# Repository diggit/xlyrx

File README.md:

# xlyrx
Hobby RC 2.4GHz receiver based on cc2500 and STM32, supporting FrSky 2 Way D-series protocol

This project is another opensource receiver for cc2500 based radios.

## Features
- FrSky 2-way (telemetry) protocol for D-series
- based on ARM MCU (STM32)
- Hardware generated high resolution ppm signal (~4 times higher, than FrSky can tranfer)
- bind time RX-TX frequency offset elimination
- high power power amplifier and high sensitivity low noise amplifier cc2500 module
- alternative power input for channels 5,6,7,8
- 2 analog inputs
- initial work on fail-safes, when signal is lost, outputs are tuned off now, user config is missing

*ready, but hardcoded for now*
- configurable ppm frequency
	- channels 1,2,5,6 are driven by one HW timer, outputs 4,5,7,8 are driven by another
	- ppm frequency is defined by 3rd timer, all channels have same frequency for now, to be able to have different ppm frequency for each group, packet timeout timer must be changed from regular timer to systick, then we'll have free HW timer to drive second group of outputs with different frequency

*HW ready, SW not yet written*
- UART (3,3V) for loading new firmware (bootloader) and RX user configuration
- UART (3,3V) for external telemetry configuration (raw or FrSky format)
- meaningful usage of LED (we have 2 of them, so use them!)

### Known issues
- if TX and RX are too close during binding, binding may not be successful (stuck in binding mode)
	- maybe some AGC tuning could help
	- workaround would be binding procedure restart

## Why?
If you sum up all that time, materials and work, why (I) build this and not buy regular FrSky receiver? For fun! To explore HW, skills... I like the possibility to modify things to way I like them. Easily add new features and make them better than regular ones...

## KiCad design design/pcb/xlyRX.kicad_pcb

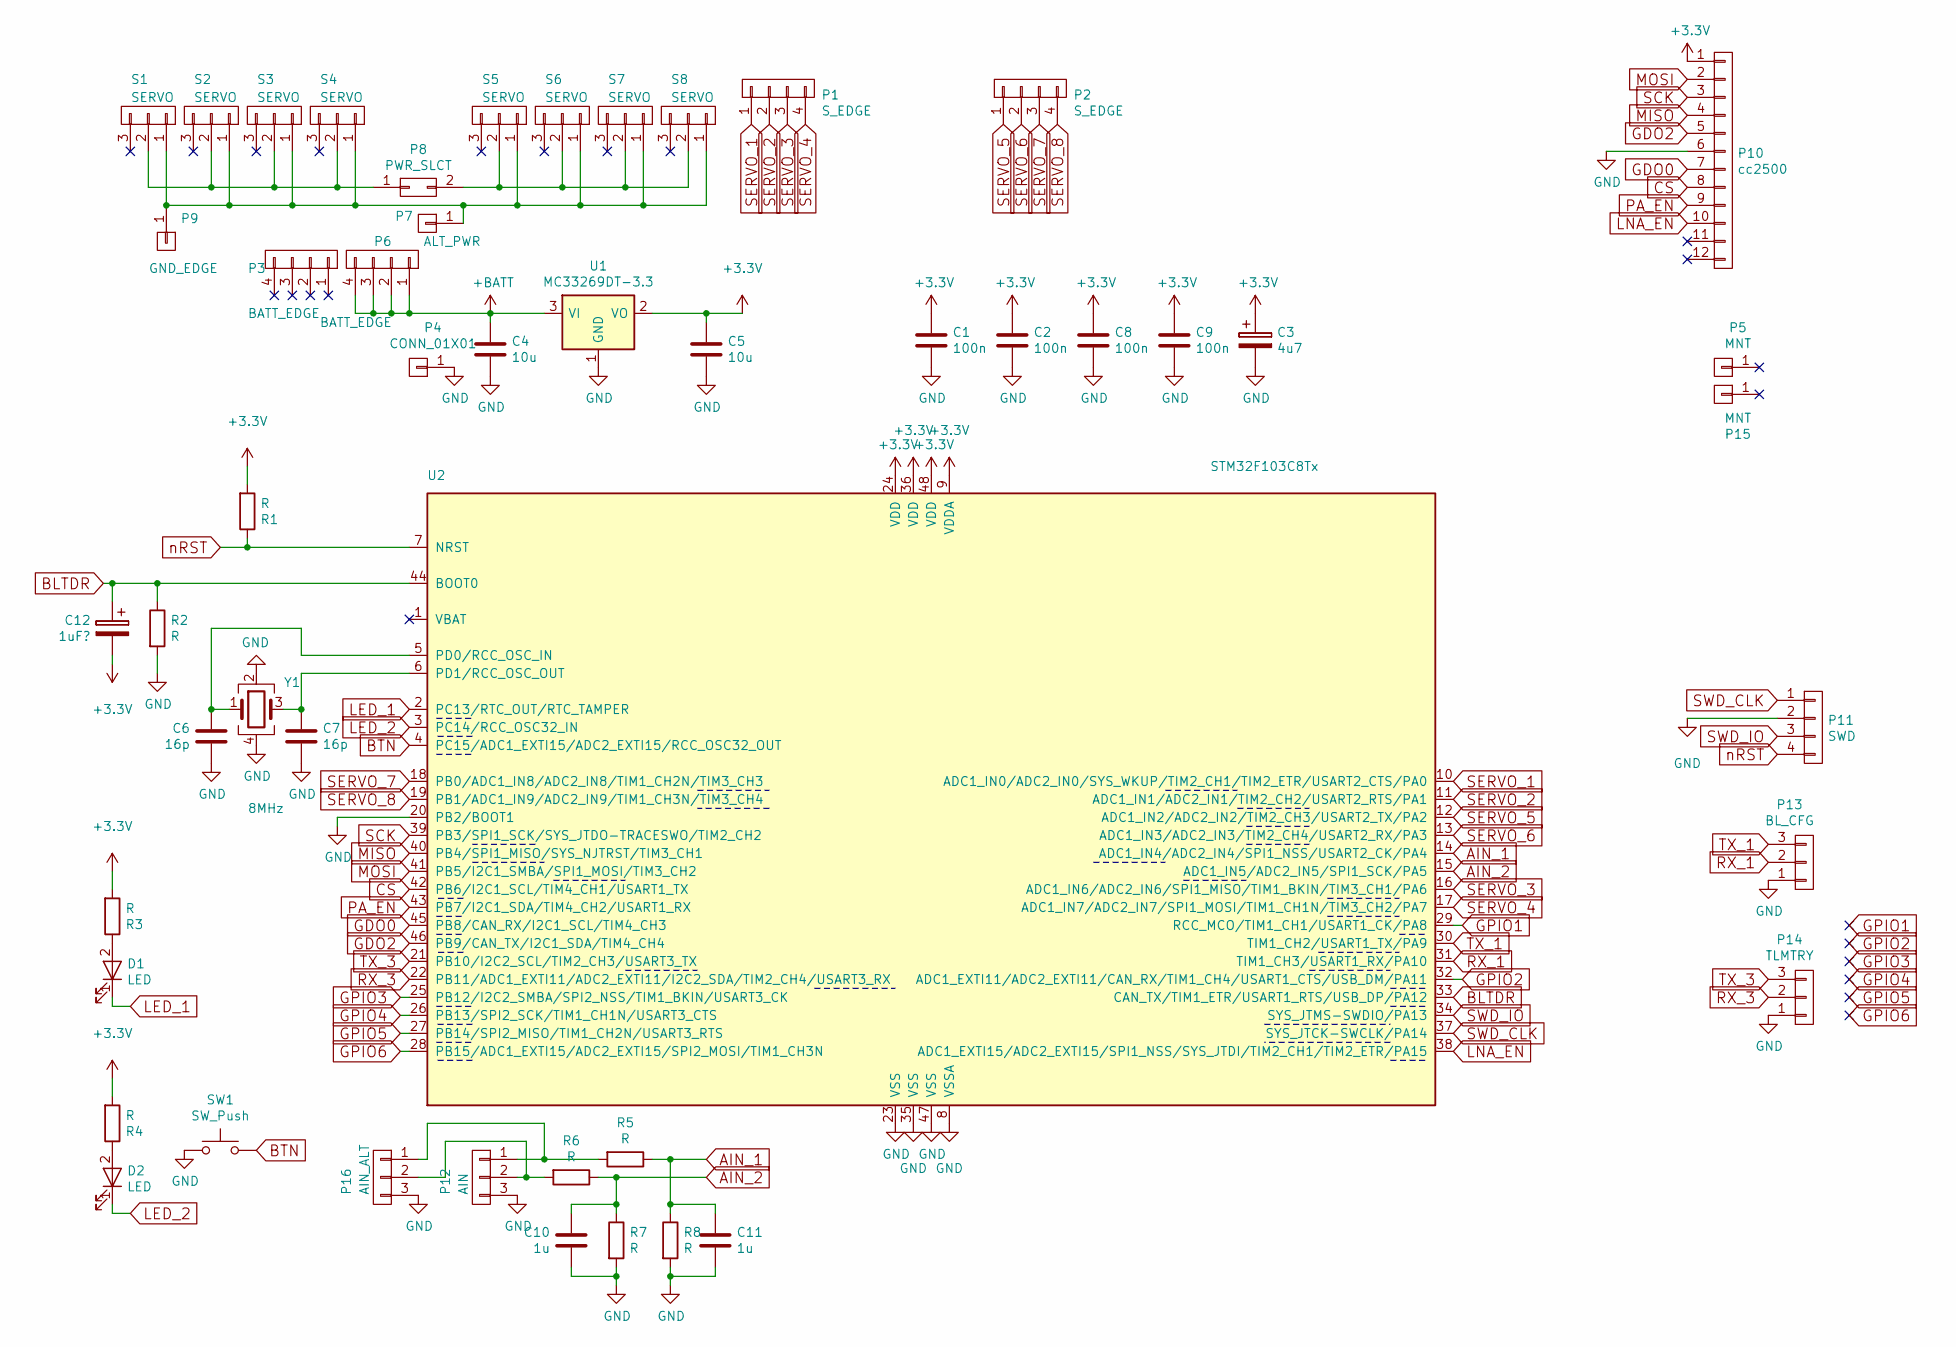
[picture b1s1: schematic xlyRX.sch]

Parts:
C1, C2, C8, C9: 100n; C_0805
C3: 4u7; C_0805
C4, C5: 10u; C_0805
C6, C7: 16p; C_0805
C10, C11: 1u; C_0805
C12: 1uF?; C_0805
D1, D2: LED; LED_0805
P1, P2: S_EDGE; SMD_conn_edge
P3, P6: BATT_EDGE; SMD_conn_edge
P4: CONN_01X01; SMD_conn_edge_1p
P5, P15: MNT; SMD_conn_edge_1p
P7: ALT_PWR; Pin_Header_Straight_1x01_Pitch2.54mm_simplified_silk
P8: PWR_SLCT; Pin_Header_Straight_1x02_Pitch2.54mm_simplified_silk
P9: GND_EDGE; SMD_conn_edge_1p
P10: cc2500; module_cc2500_PA_LNA_small_pads
P11: SWD; SMD_conn_edge
P12: AIN; SMD_conn_edge_3
P13: BL_CFG; Pin_Header_Straight_1x03
P14: TLMTRY; Pin_Header_Straight_1x03
P16: AIN_ALT; Pin_Header_Straight_1x03_Pitch2.54mm
R1, R2, R3, R4, R5, R6, R7, R8: R; R_0805
S1, S2, S3, S4, S5, S6, S7, S8: SERVO; Pin_Header_Straight_1x03_Pitch2.54mm_simplified_silk
SW1: SW_Push; SW_SPST_REED_CT05-XXXX-J1
U1: MC33269DT-3.3; TO-252-2Lead
U2: STM32F103C8Tx; LQFP-48_7x7mm_Pitch0.5mm
Y1: 8MHz; Crystal_SMD_5032_4Pads

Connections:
+3V3: C1.1, C2.1, C3.1, C5.1, C8.1, C9.1, C12.2, P10.1, R1.2, R3.2, R4.2, U1.2 (VO), U2.9 (VDDA), U2.24 (VDD), U2.36 (VDD), U2.48 (VDD)
+BATT: C4.1, P6.1, P6.2, P6.3, P6.4, U1.3 (VI)
AIN_1: C11.1, R5.1, R8.1, U2.14 (ADC1_IN4/ADC2_IN4/SPI1_NSS/USART2_CK/PA4)
AIN_2: C10.1, R6.1, R7.1, U2.15 (ADC1_IN5/ADC2_IN5/SPI1_SCK/PA5)
BLTDR: C12.1, R2.1, U2.33 (CAN_TX/TIM1_ETR/USART1_RTS/USB_DP/PA12), U2.44 (BOOT0)
BTN: SW1.2, U2.4 (PC15/ADC1_EXTI15/ADC2_EXTI15/RCC_OSC32_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)
CS: P10.8, U2.42 (PB6/I2C1_SCL/TIM4_CH1/USART1_TX)
GDO0: P10.7, U2.45 (PB8/CAN_RX/I2C1_SCL/TIM4_CH3)
GDO2: P10.5, U2.46 (PB9/CAN_TX/I2C1_SDA/TIM4_CH4)
GND: C1.2, C2.2, C3.2, C4.2, C5.2, C6.2, C7.2, C8.2, C9.2, C10.2, C11.2, P4.1, P10.6, P11.2, P12.3, P13.1, P14.1, P16.3, R2.2, R7.2, R8.2, SW1.1, U1.1 (GND), U2.8 (VSSA), U2.20 (PB2/BOOT1), U2.23 (VSS), U2.35 (VSS), U2.47 (VSS), Y1.2, Y1.4
GPIO1: U2.29 (RCC_MCO/TIM1_CH1/USART1_CK/PA8)
GPIO2: U2.32 (ADC1_EXTI11/ADC2_EXTI11/CAN_RX/TIM1_CH4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)
GPIO3: U2.25 (PB12/I2C2_SMBA/SPI2_NSS/TIM1_BKIN/USART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)
GPIO4: U2.26 (PB13/SPI2_SCK/TIM1_CH1N/USART3_CTS)
GPIO5: U2.27 (PB14/SPI2_MISO/TIM1_CH2N/USART3_RTS)
GPIO6: U2.28 (PB15/ADC1_EXTI15/ADC2_EXTI15/SPI2_MOSI/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)
LED_1: D1.1 (K), U2.2 (PC13/RTC_OUT/RTC_TAMPER)
LED_2: D2.1 (K), U2.3 (PC14/RCC_OSC32_IN)
LNA_EN: P10.10, U2.38 (ADC1_EXTI15/ADC2_EXTI15/SPI1_NSS/SYS_JT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)
MISO: P10.4, U2.40 (PB4/SPI1_MISO/SYS_NJTRST/TIM3_CH1)
MOSI: P10.2, U2.41 (PB5/I2C1_SMBA/SPI1_MOSI/TIM3_CH2)
unnamed: C6.1, U2.5 (PD0/RCC_OSC_IN), Y1.1
unnamed: C7.1, U2.6 (PD1/RCC_OSC_OUT), Y1.3
unnamed: D1.2 (A), R3.1
unnamed: D2.2 (A), R4.1
unnamed: P7.1, P9.1, S1.1, S2.1, S3.1, S4.1, S5.1, S6.1, S7.1, S8.1
unnamed: P8.1, S1.2, S2.2, S3.2, S4.2
unnamed: P8.2, S5.2, S6.2, S7.2, S8.2
unnamed: P12.1, P16.1, R5.2
unnamed: P12.2, P16.2, R6.2
PA_EN: P10.9, U2.43 (PB7/I2C1_SDA/TIM4_CH2/USART1_RX)
RX_1: P13.2, U2.31 (TIM1_CH3/USART1_RX/PA10)
RX_3: P14.2, U2.22 (PB11/ADC1_EXTI11/ADC2_EXTI11/I2C2_SDA/T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)
SCK: P10.3, U2.39 (PB3/SPI1_SCK/SYS_JTDO-TRACESWO/TIM2_CH2)
SERVO_1: P1.1, U2.10 (ADC1_IN0/ADC2_IN0/SYS_WKUP/TIM2_CH1/TIM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)
SERVO_2: P1.2, U2.11 (ADC1_IN1/ADC2_IN1/TIM2_CH2/USART2_RTS/P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)
SERVO_3: P1.3, U2.16 (ADC1_IN6/ADC2_IN6/SPI1_MISO/TIM1_BKIN/T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)
SERVO_4: P1.4, U2.17 (ADC1_IN7/ADC2_IN7/SPI1_MOSI/TIM1_CH1N/T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)
SERVO_5: P2.1, U2.12 (ADC1_IN2/ADC2_IN2/TIM2_CH3/USART2_TX/PA2)
SERVO_6: P2.2, U2.13 (ADC1_IN3/ADC2_IN3/TIM2_CH4/USART2_RX/PA3)
SERVO_7: P2.3, U2.18 (PB0/ADC1_IN8/ADC2_IN8/TIM1_CH2N/TIM3_CH3)
SERVO_8: P2.4, U2.19 (PB1/ADC1_IN9/ADC2_IN9/TIM1_CH3N/TIM3_CH4)
SWD_CLK: P11.1, U2.37 (SYS_JTCK-SWCLK/PA14)
SWD_IO: P11.3, U2.34 (SYS_JTMS-SWDIO/PA13)
TX_1: P13.3, U2.30 (TIM1_CH2/USART1_TX/PA9)
TX_3: P14.3, U2.21 (PB10/I2C2_SCL/TIM2_CH3/USART3_TX)
nRST: P11.4, R1.1, U2.7 (NRST)

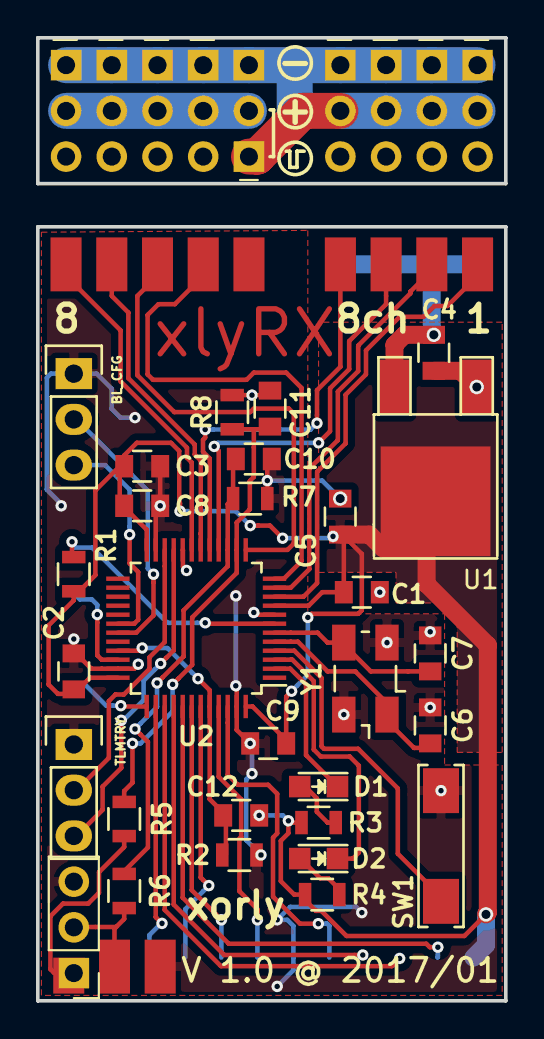
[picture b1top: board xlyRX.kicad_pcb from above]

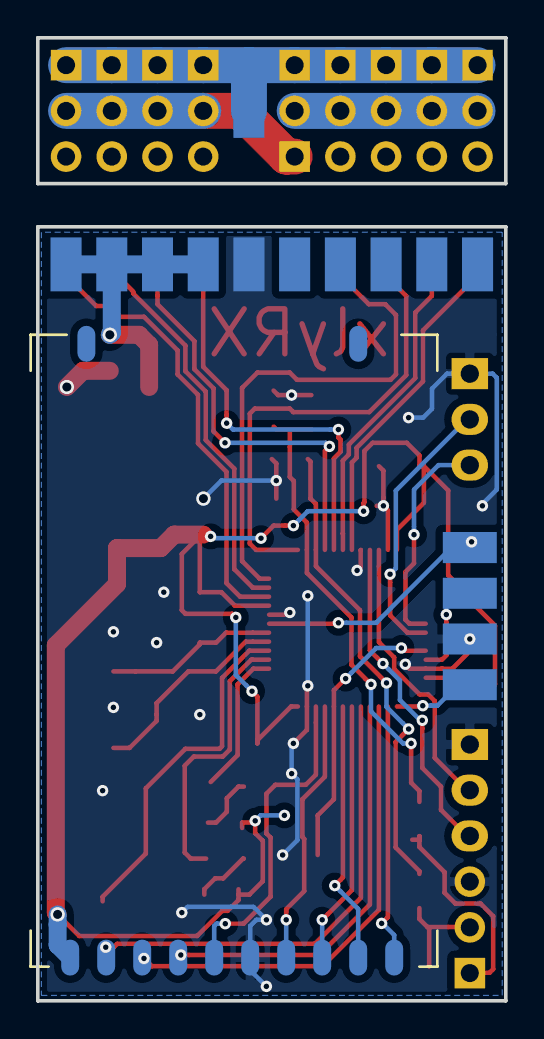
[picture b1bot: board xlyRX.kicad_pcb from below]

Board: 2 copper layers, 26.0 x 53.5 mm, 50 parts (7 on the bottom side), 41 nets.

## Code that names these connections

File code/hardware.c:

// Copyright (c) 2017 Patrik Bachan
//
// GNU GENERAL PUBLIC LICENSE
//    Version 3, 29 June 2007
//
// This program is free software: you can redistribute it and/or modify
// it under the terms of the GNU General Public License as published by
// the Free Software Foundation, either version 3 of the License, or
// (at your option) any later version.
//
// This program is distributed in the hope that it will be useful,
// but WITHOUT ANY WARRANTY; without even the implied warranty of
// MERCHANTABILITY or FITNESS FOR A PARTICULAR PURPOSE.  See the
// GNU General Public License for more details.
//
// You should have received a copy of the GNU General Public License
// along with this program.  If not, see <http://www.gnu.org/licenses/>.

#include "hardware.h"
#include "misc.h"


void gpio_init(void)
{
	bit_set(RCC->APB2ENR, \
			RCC_APB2ENR_IOPAEN |\
			RCC_APB2ENR_IOPBEN |\
			RCC_APB2ENR_IOPCEN |\
			RCC_APB2ENR_AFIOEN);// enable clock to ports A,B,C, USART1, AFIO

	AFIO->MAPR =	AFIO_MAPR_SPI1_REMAP | AFIO_MAPR_SWJ_CFG_JTAGDISABLE;

	GPIOA->CRL =	\
					//PA0	S0	(TIM2_CH1)
					GPIO_ALTERNATE			<<GPIO_CRL_MODE0_Pos|\
					//PA1	S1	(TIM2_CH2)
					GPIO_ALTERNATE			<<GPIO_CRL_MODE1_Pos|\
					//PA2	S5	(TIM2_CH3)
					GPIO_ALTERNATE			<<GPIO_CRL_MODE2_Pos|\
					//PA3	S6	(TIM2_CH4)
					GPIO_ALTERNATE			<<GPIO_CRL_MODE3_Pos|\
					//PA4	AIN_1	(ADC_IN4)
					GPIO_INPUT_ANALOG		<<GPIO_CRL_MODE4_Pos|\
					//PA5	AIN_2	(ADC_IN5)
					GPIO_INPUT_ANALOG		<<GPIO_CRL_MODE5_Pos|\
					//PA6	S3	(TIM3_CH1)
					GPIO_ALTERNATE			<<GPIO_CRL_MODE6_Pos|\
					//PA7	S4	(TIM3_CH2)
					GPIO_ALTERNATE			<<GPIO_CRL_MODE7_Pos;

	GPIOA->CRH = 	\
					//PA8	GPIO1	(GPIO)
					GPIO_INPUT				<<GPIO_CRH_MODE8_Pos|\
					//PA9	BL_FG_TX	(USART1_TX)
					GPIO_ALTERNATE			<<GPIO_CRH_MODE9_Pos|\
					//PA10	BL_FG_RX	(USART1_RX)
					GPIO_INPUT_PULL_UP_DOWN	<<GPIO_CRH_MODE10_Pos|\
					//PA11	GPIO2	(GPIO)
					GPIO_INPUT				<<GPIO_CRH_MODE11_Pos|\
					//PA12	BTLDR	(GPIO)
					GPIO_OUTPUT				<<GPIO_CRH_MODE12_Pos|\
					/*SWD
					GPIO_INPUT				<<GPIO_CRH_MODE13_Pos|\
					GPIO_INPUT				<<GPIO_CRH_MODE14_Pos|\
					*/
					//PA15	LNA_EN	(GPIO)
					GPIO_OUTPUT				<<GPIO_CRH_MODE15_Pos;

	GPIOA->ODR =	\
					//PA10 PUP
					GPIO_ODR_ODR10;

	GPIOB->CRL =	\
					//PB0	S7		(TIM3_CH3)
					GPIO_ALTERNATE			<<GPIO_CRL_MODE0_Pos|\
					//PB1	S8		(TIM3_CH4)
					GPIO_INPUT				<<GPIO_CRL_MODE1_Pos|\
					//PB2	BOOT1
					/*GPIO_INPUT				<<GPIO_CRL_MODE2_Pos|\*/
					//PB3	SCK		(SPI1_SCK) REMAP!
					GPIO_ALTERNATE_10MHz	<<GPIO_CRL_MODE3_Pos|\
					//PB4	MISO	(SPI1_MISO) REMAP!
					GPIO_INPUT				<<GPIO_CRL_MODE4_Pos|\
					//PB5	MOSI	(SPI1_MOSI) REMAP!
					GPIO_ALTERNATE_10MHz	<<GPIO_CRL_MODE5_Pos|\
					//PB6	CS		(GPIO)
					GPIO_OUTPUT_2MHz		<<GPIO_CRL_MODE6_Pos|\
					//PB7	PA_EN	(GPIO)
					GPIO_OUTPUT				<<GPIO_CRL_MODE7_Pos;

	GPIOB->CRH = 	\
					//PB8	GDO0	(GPIO)
					GPIO_INPUT				<<GPIO_CRH_MODE8_Pos|\
					//PB9	GDO2	(GPIO)
					GPIO_INPUT				<<GPIO_CRH_MODE9_Pos|\
					//PB10	TLMTRY_TX	(USART3_TX)
					GPIO_ALTERNATE			<<GPIO_CRH_MODE10_Pos|\
					//PB11	TLMTRY_RX	(USART3_RX)
					GPIO_INPUT_PULL_UP_DOWN	<<GPIO_CRH_MODE11_Pos|\
					//PB12	GPIO3	(GPIO)
					GPIO_INPUT				<<GPIO_CRH_MODE12_Pos|\
					//PB13	GPIO4	(GPIO)
					GPIO_INPUT				<<GPIO_CRH_MODE13_Pos|\
					//PB14	GPIO5	(GPIO)
					GPIO_INPUT				<<GPIO_CRH_MODE14_Pos|\
					//PB15	GPIO6	(GPIO)
					GPIO_INPUT				<<GPIO_CRH_MODE15_Pos;

	GPIOB->ODR =	\
					//PB6	HIGH
					GPIO_ODR_ODR6|\
					//PB11	PUP
					GPIO_ODR_ODR11;

	//only pins 13,14,15 present
	GPIOC->CRH = 	\
					//PC13	LED_1	(GPIO)
					GPIO_OUTPUT				<<GPIO_CRH_MODE13_Pos|\
					//PC14	LED_2	(GPIO)
					GPIO_OUTPUT				<<GPIO_CRH_MODE14_Pos|\
					//PC15	BTN		(GPIO)
					GPIO_INPUT_PULL_UP_DOWN	<<GPIO_CRH_MODE15_Pos;

	GPIOC->ODR =	\
					//PC13	LED(OFF)
					GPIO_ODR_ODR13|\
					//PC14	LED(OFF)
					GPIO_ODR_ODR14|\
					//PC15	BTN PUP
					GPIO_ODR_ODR15;


	//enable EXTI inttterupt for GDOs
	AFIO->EXTICR[2]=AFIO_EXTICR3_EXTI8_PB | AFIO_EXTICR3_EXTI9_PB;
}

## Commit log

2017-02-14 initial sources and design commit
2017-02-14 pcb development version
2017-02-15 reload all KiCAD symbol libraries
2017-02-15 move gpio controls into separate library
2017-02-15 fix Makefile, -flto produced bad binary->HardFaults , disable for now
2017-02-15 protocol cleanup, less debug output, more comments
2017-02-15 README update
2017-02-21 readme cleanup
2017-02-21 add analog input reading
2017-02-21 improve TX timing (interrupt driven), release outputs on signal loss (initial fail-safe work)
2017-02-21 update README (fail-safe, LEDs)
2017-02-25 change cc2500 LNA/PA switching commands order to give at least some deadtime
2017-02-25 do not process exceptions if irq enable called on them
2017-02-25 add systick register structure and bit definitions
2017-02-25 add systick(non blocking) LED blink functionality
2017-02-28 add ability to read button state
2017-03-03 release nSRST signal on debug/flashing exit
2017-03-03 add flashing through serial bootloader to Makefile (BLburn)
2017-03-03 fix button state polarity
2017-03-03 add reset by uart
2017-03-03 add led status indication, tune cc2500 settings, 100m range tested - works well
2017-03-03 modify ftdi config to be able to set n?RST outputs to Hi-z
2017-03-03 add SCB registers access
2017-03-03 add systick button handling (untested)
2017-03-04 modify makefile to erase only necessary amount of flash pages during BLburn
2017-03-04 fix makefile comments
2017-07-14 disable debug messages
2017-07-14 set PPM frequency to 200Hz, fix const
2017-07-15 rename currently supported protocol from 2W to D
2017-07-15 fix all protocol renaming from 2W to D, rename BIND constants to protocol specific names
